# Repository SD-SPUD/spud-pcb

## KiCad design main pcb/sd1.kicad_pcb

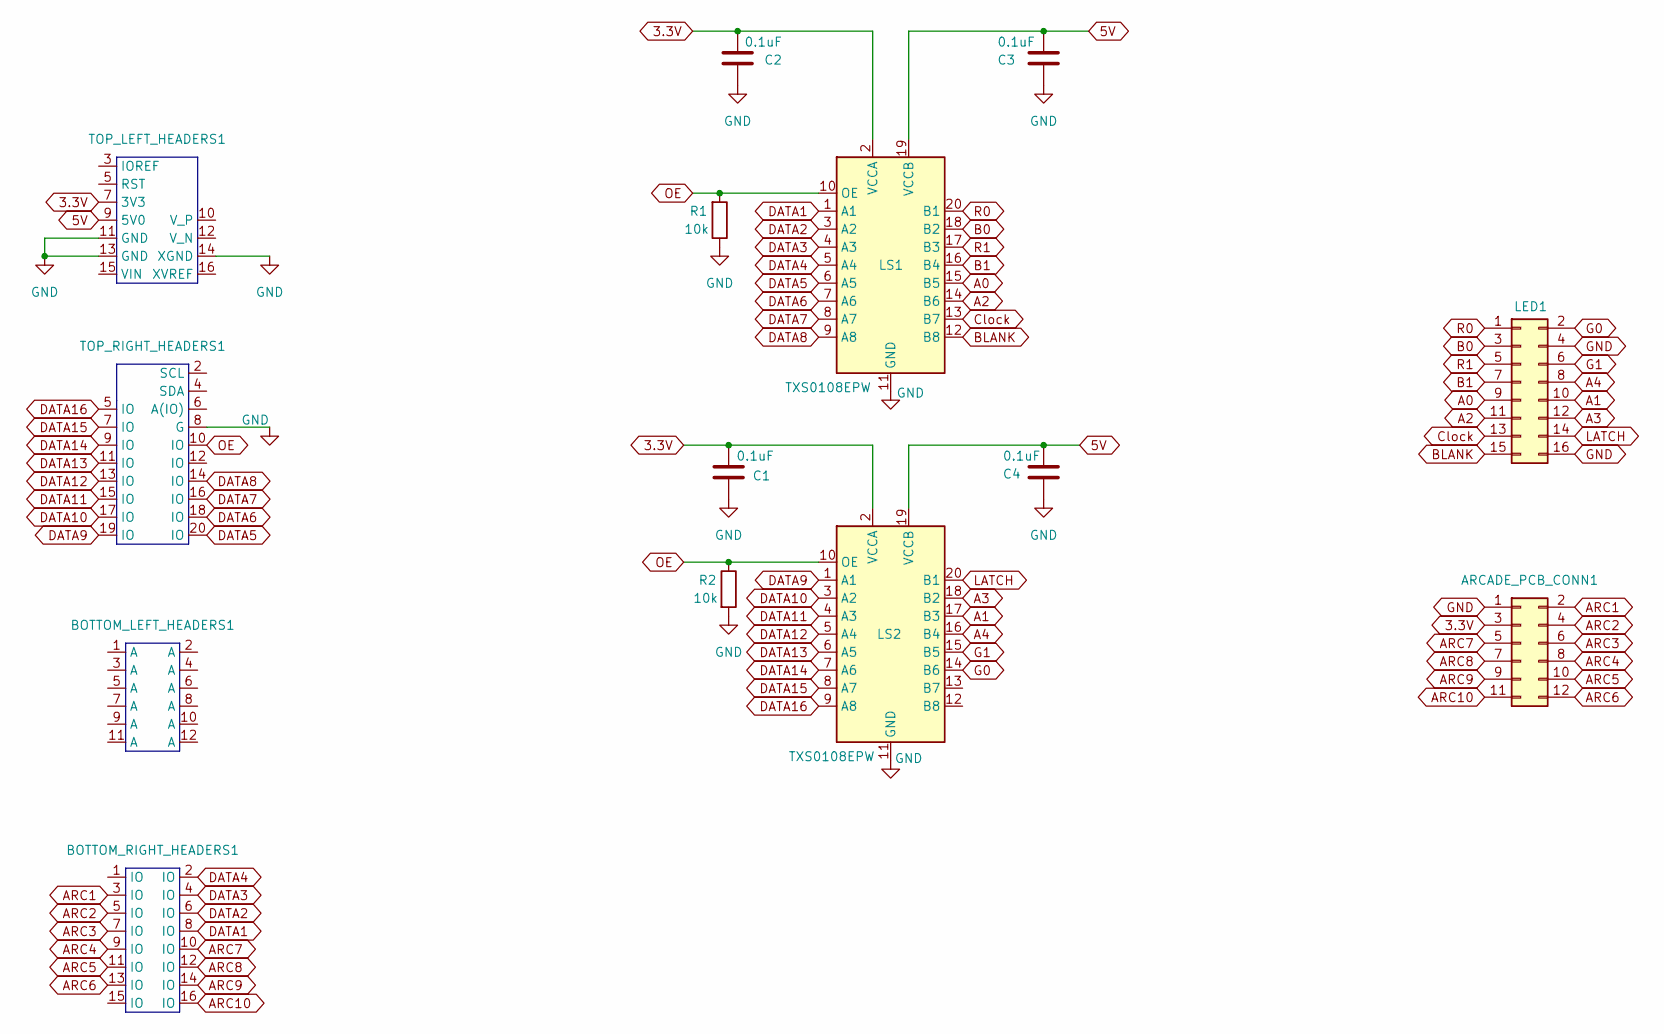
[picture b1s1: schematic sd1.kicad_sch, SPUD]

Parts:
ARCADE_PCB_CONN1: Conn_02x06_Top_Bottom; PinHeader_2x06_P2.54mm_Vertical
BOTTOM_LEFT_HEADERS1: PinHeader_2x06_P2.54mm_Vertical
BOTTOM_RIGHT_HEADERS1: PinHeader_2x08_P2.54mm_Vertical
C1, C2, C3, C4: 0.1uF; C_0805_2012Metric
LED1: Conn_02x08_Odd_Even; PinHeader_2x08_P2.54mm_Vertical
LS1, LS2: TXS0108EPW; TSSOP-20_4.4x6.5mm_P0.65mm
R1, R2: 10k; R_0805_2012Metric
TOP_LEFT_HEADERS1: PinHeader_2x08_P2.54mm_Vertical
TOP_RIGHT_HEADERS1: PinHeader_2x10_P2.54mm_Vertical

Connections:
3.3V: ARCADE_PCB_CONN1.3, C1.1, C2.1, LS1.2 (VCCA), LS2.2 (VCCA), TOP_LEFT_HEADERS1.7 (3V3)
5V: C3.1, C4.1, LS1.19 (VCCB), LS2.19 (VCCB), TOP_LEFT_HEADERS1.9 (5V0)
A0: LED1.9, LS1.15 (B5)
A1: LED1.10, LS2.17 (B3)
A2: LED1.11, LS1.14 (B6)
A3: LED1.12, LS2.18 (B2)
A4: LED1.8, LS2.16 (B4)
ARC1: ARCADE_PCB_CONN1.2, BOTTOM_RIGHT_HEADERS1.3 (IO)
ARC2: ARCADE_PCB_CONN1.4, BOTTOM_RIGHT_HEADERS1.5 (IO)
ARC3: ARCADE_PCB_CONN1.6, BOTTOM_RIGHT_HEADERS1.7 (IO)
ARC4: ARCADE_PCB_CONN1.8, BOTTOM_RIGHT_HEADERS1.9 (IO)
ARC5: ARCADE_PCB_CONN1.10, BOTTOM_RIGHT_HEADERS1.11 (IO)
ARC6: ARCADE_PCB_CONN1.12, BOTTOM_RIGHT_HEADERS1.13 (IO)
ARC7: ARCADE_PCB_CONN1.5, BOTTOM_RIGHT_HEADERS1.10 (IO)
ARC8: ARCADE_PCB_CONN1.7, BOTTOM_RIGHT_HEADERS1.12 (IO)
ARC9: ARCADE_PCB_CONN1.9, BOTTOM_RIGHT_HEADERS1.14 (IO)
ARC10: ARCADE_PCB_CONN1.11, BOTTOM_RIGHT_HEADERS1.16 (IO)
B0: LED1.3, LS1.18 (B2)
B1: LED1.7, LS1.16 (B4)
BLANK: LED1.15, LS1.12 (B8)
Clock: LED1.13, LS1.13 (B7)
DATA1: BOTTOM_RIGHT_HEADERS1.8 (IO), LS1.1 (A1)
DATA2: BOTTOM_RIGHT_HEADERS1.6 (IO), LS1.3 (A2)
DATA3: BOTTOM_RIGHT_HEADERS1.4 (IO), LS1.4 (A3)
DATA4: BOTTOM_RIGHT_HEADERS1.2 (IO), LS1.5 (A4)
DATA5: LS1.6 (A5), TOP_RIGHT_HEADERS1.20 (IO)
DATA6: LS1.7 (A6), TOP_RIGHT_HEADERS1.18 (IO)
DATA7: LS1.8 (A7), TOP_RIGHT_HEADERS1.16 (IO)
DATA8: LS1.9 (A8), TOP_RIGHT_HEADERS1.14 (IO)
DATA9: LS2.1 (A1), TOP_RIGHT_HEADERS1.19 (IO)
DATA10: LS2.3 (A2), TOP_RIGHT_HEADERS1.17 (IO)
DATA11: LS2.4 (A3), TOP_RIGHT_HEADERS1.15 (IO)
DATA12: LS2.5 (A4), TOP_RIGHT_HEADERS1.13 (IO)
DATA13: LS2.6 (A5), TOP_RIGHT_HEADERS1.11 (IO)
DATA14: LS2.7 (A6), TOP_RIGHT_HEADERS1.9 (IO)
DATA15: LS2.8 (A7), TOP_RIGHT_HEADERS1.7 (IO)
DATA16: LS2.9 (A8), TOP_RIGHT_HEADERS1.5 (IO)
G0: LED1.2, LS2.14 (B6)
G1: LED1.6, LS2.15 (B5)
GND: ARCADE_PCB_CONN1.1, C1.2, C2.2, C3.2, C4.2, LED1.4, LED1.16, LS1.11 (GND), LS2.11 (GND), R1.2, R2.2, TOP_LEFT_HEADERS1.11 (GND), TOP_LEFT_HEADERS1.13 (GND), TOP_LEFT_HEADERS1.14 (XGND), TOP_RIGHT_HEADERS1.8 (G)
LATCH: LED1.14, LS2.20 (B1)
OE: LS1.10 (OE), LS2.10 (OE), R1.1, R2.1, TOP_RIGHT_HEADERS1.10 (IO)
R0: LED1.1, LS1.20 (B1)
R1: LED1.5, LS1.17 (B3)

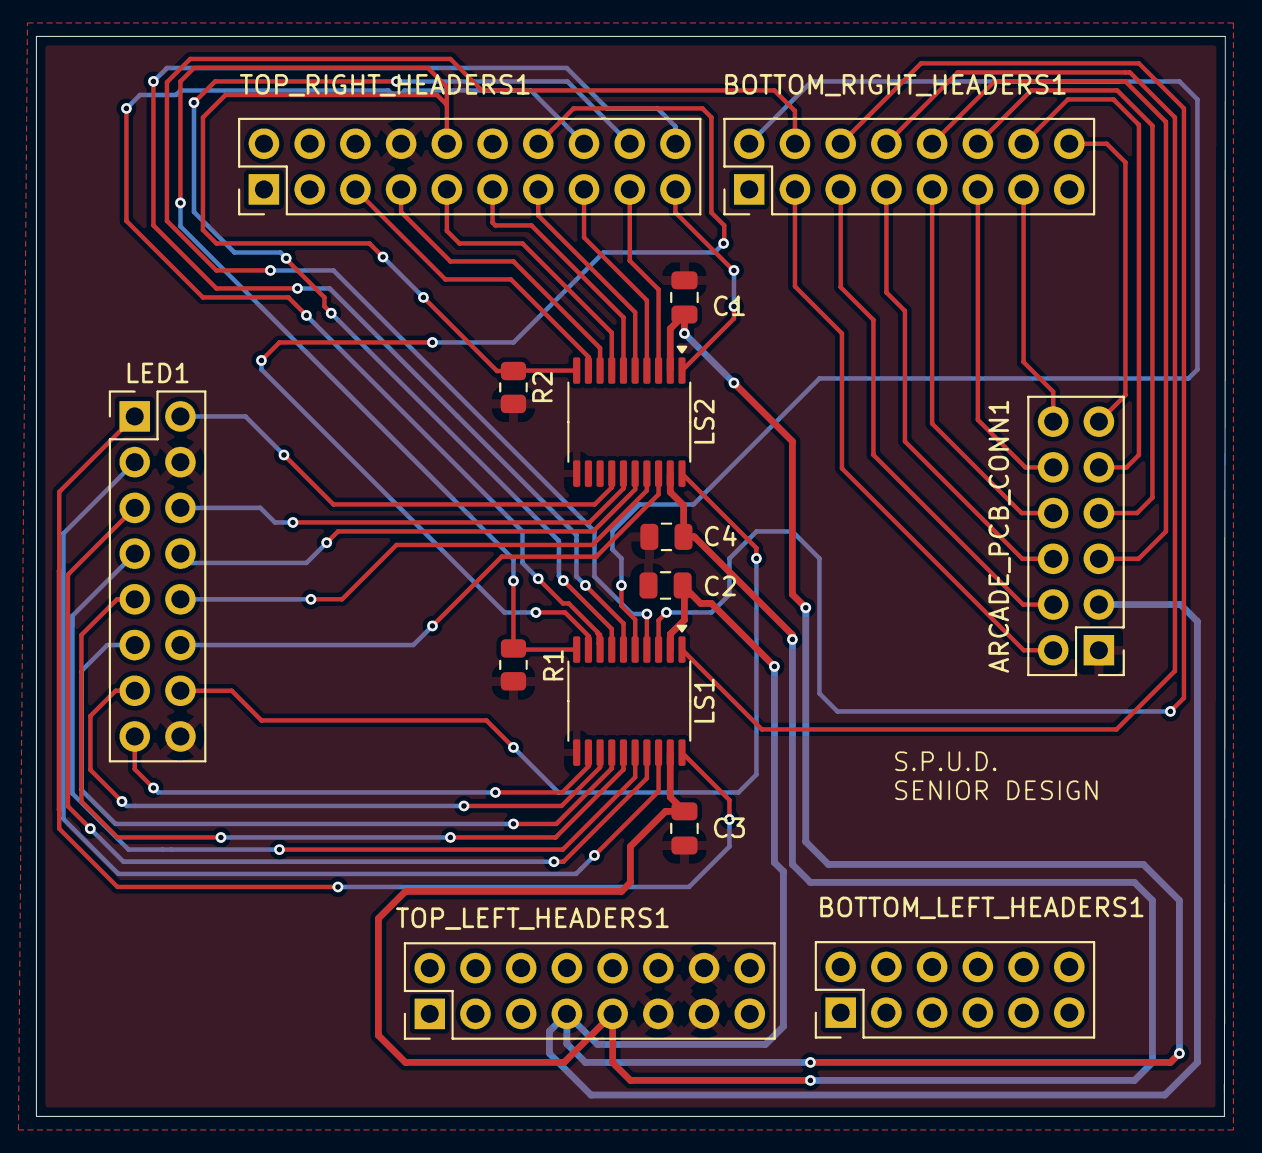
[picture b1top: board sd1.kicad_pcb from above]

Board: 2 copper layers, 66.1 x 60.0 mm, 14 parts (0 on the bottom side), 44 nets.

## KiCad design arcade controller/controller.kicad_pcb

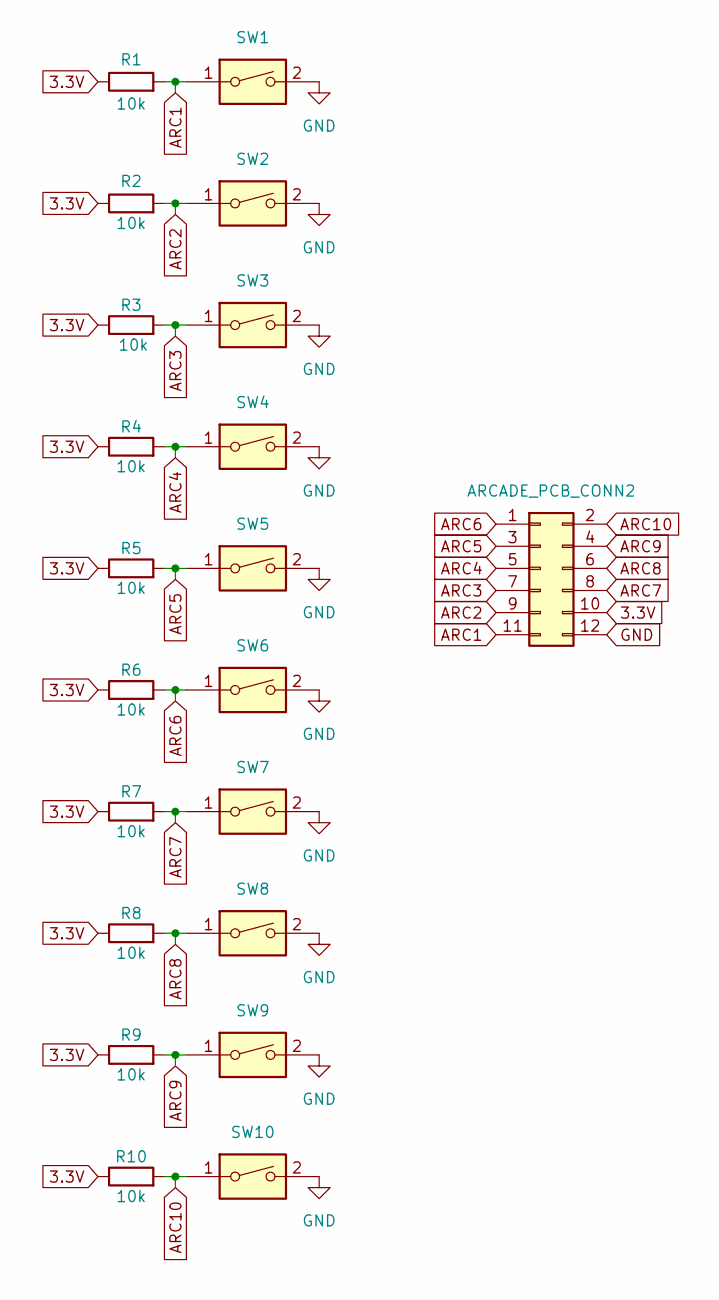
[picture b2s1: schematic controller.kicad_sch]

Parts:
ARCADE_PCB_CONN2: Conn_02x06_Odd_Even; PinHeader_2x06_P2.54mm_Vertical
R1, R2, R3, R4, R5, R6, R7, R8, R9, R10: 10k; R_0805_2012Metric
SW1, SW2, SW3, SW4, SW5, SW6, SW7, SW8, SW9, SW10: SW_DIP_x01; pads

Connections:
3.3V: ARCADE_PCB_CONN2.10, R1.1, R2.1, R3.1, R4.1, R5.1, R6.1, R7.1, R8.1, R9.1, R10.1
ARC1: ARCADE_PCB_CONN2.11, R1.2, SW1.1
ARC2: ARCADE_PCB_CONN2.9, R2.2, SW2.1
ARC3: ARCADE_PCB_CONN2.7, R3.2, SW3.1
ARC4: ARCADE_PCB_CONN2.5, R4.2, SW4.1
ARC5: ARCADE_PCB_CONN2.3, R5.2, SW5.1
ARC6: ARCADE_PCB_CONN2.1, R6.2, SW6.1
ARC7: ARCADE_PCB_CONN2.8, R7.2, SW7.1
ARC8: ARCADE_PCB_CONN2.6, R8.2, SW8.1
ARC9: ARCADE_PCB_CONN2.4, R9.2, SW9.1
ARC10: ARCADE_PCB_CONN2.2, R10.2, SW10.1
GND: ARCADE_PCB_CONN2.12, SW1.2, SW2.2, SW3.2, SW4.2, SW5.2, SW6.2, SW7.2, SW8.2, SW9.2, SW10.2

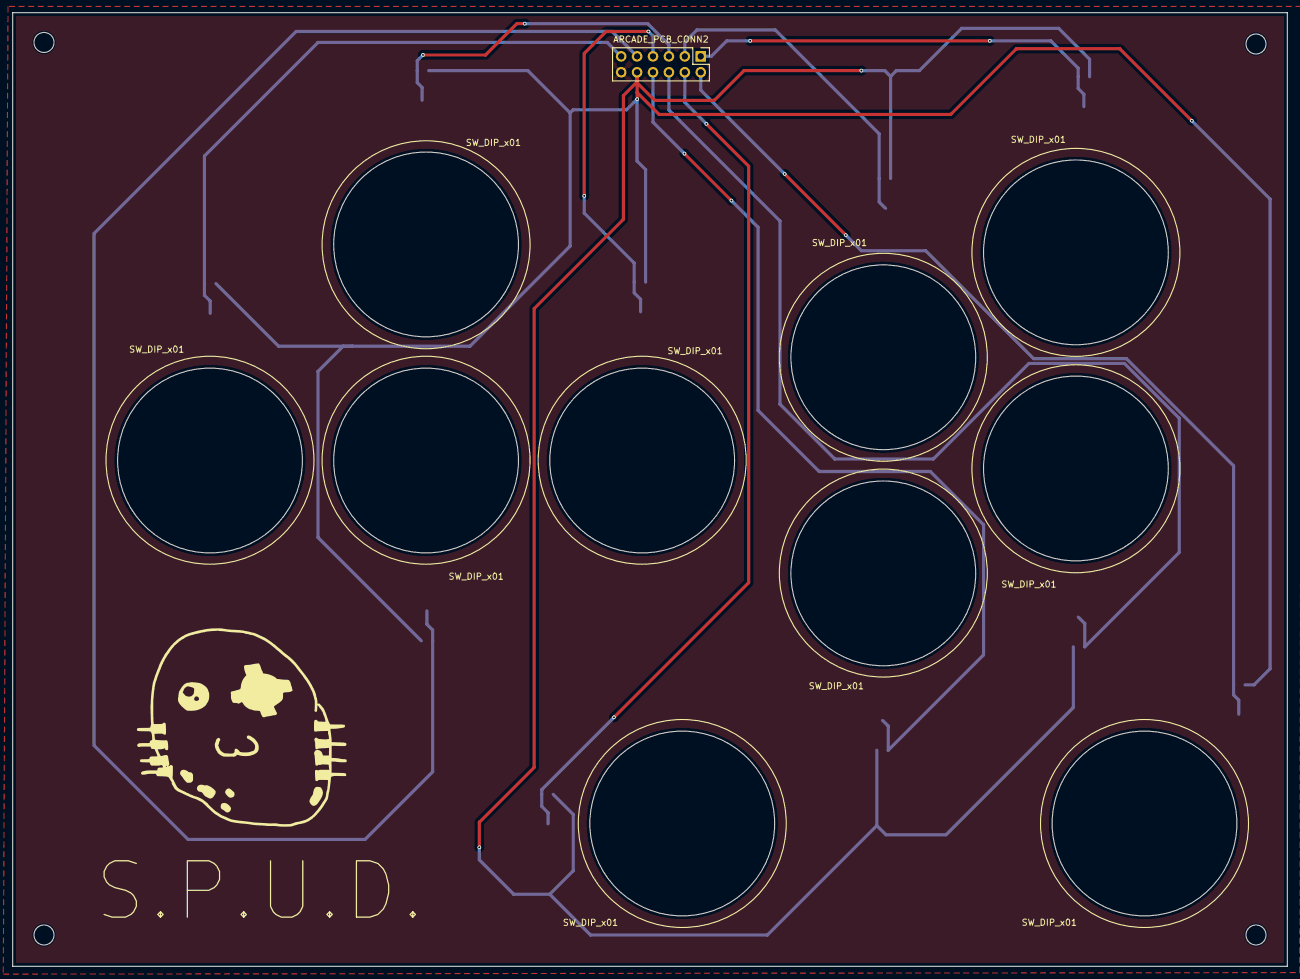
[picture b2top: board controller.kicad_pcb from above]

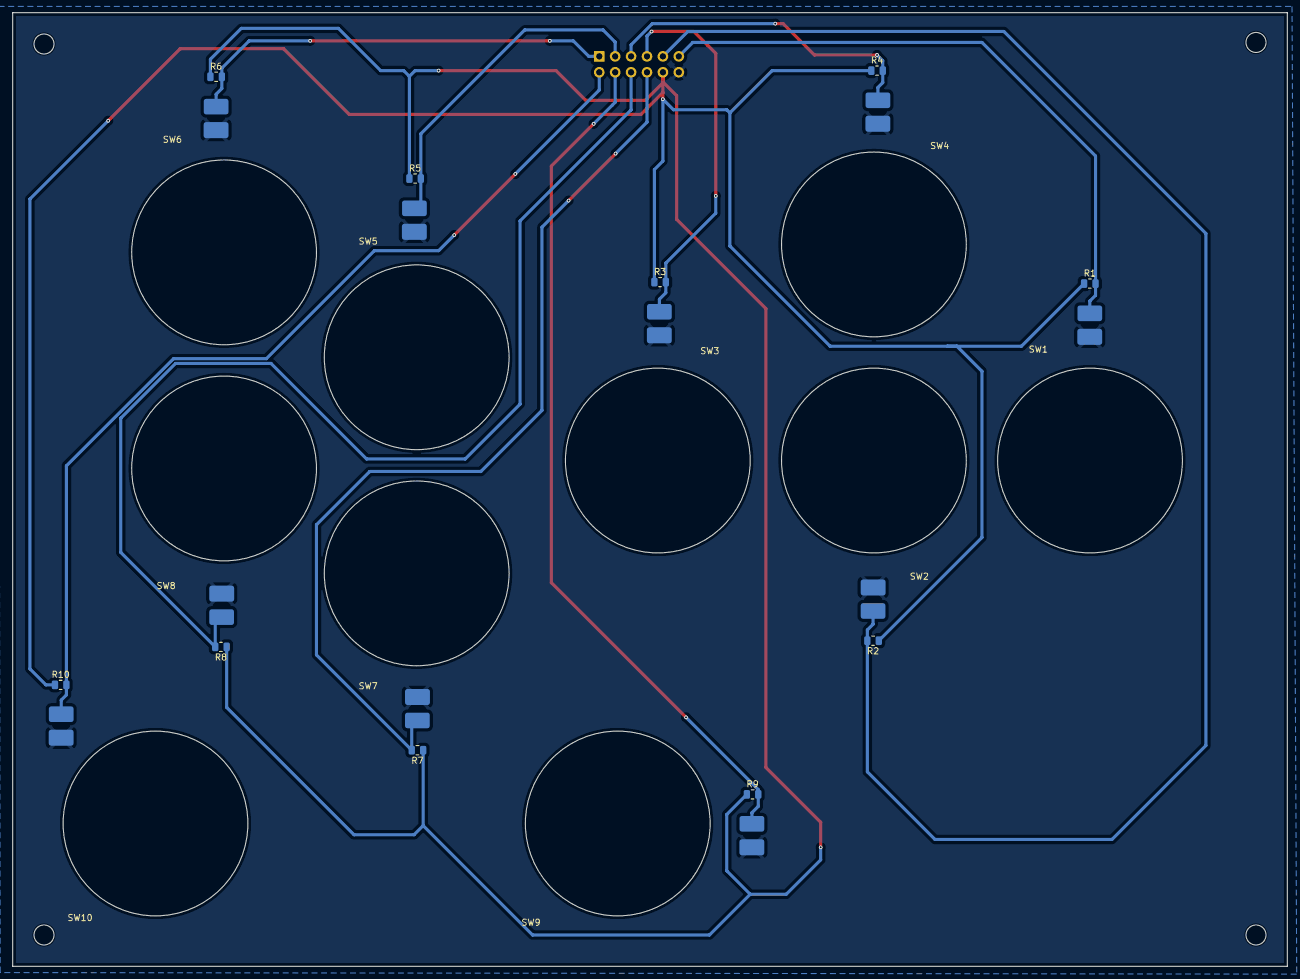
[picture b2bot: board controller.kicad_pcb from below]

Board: 2 copper layers, 203.5 x 152.2 mm, 21 parts (20 on the bottom side), 12 nets.

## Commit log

2025-08-25 main board
2025-08-25 controller board
2025-08-25 create main pcb folder
2025-08-25 main pcb
2025-09-01 spud main board
2025-09-01 remove bugged board
2025-09-01 arcade board
2025-09-01 fixed con
2025-09-01 fixed sch
2025-09-01 fixed con2
2025-09-04 wired new connector
2025-09-04 updated main pcb with new connector
2025-09-04 updated main board with new connector
2025-09-04 updated controller with new connector
2025-09-12 update arcade controller
2025-09-12 update main pcb
